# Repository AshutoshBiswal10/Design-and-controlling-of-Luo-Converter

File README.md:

# Comparative Analysis of Control Strategies for Enhancing the Performance of a DC-DC Luo Converter

This repository presents the mathematical modeling, small-signal analysis, controller design, and simulation of a **Positive Output Luo Converter (POLC)** under closed-loop voltage regulation using MATLAB/Simulink.

The project investigates the performance of three different control strategies:

- Proportional-Integral-Derivative (PID)
- Two-Degree-of-Freedom PID (2-DOF PID)
- Three-Degree-of-Freedom PID (3-DOF PID)

The controllers are evaluated based on transient response, overshoot, gain margin, phase margin, and overall voltage regulation performance.

---

## Project Overview

Positive Output Luo Converters (POLCs) are widely employed in renewable energy systems, electric vehicles, and high-gain DC-DC conversion applications due to their high voltage conversion ratio, low output ripple, and positive output polarity.

However, the nonlinear switching dynamics of the converter make accurate voltage regulation challenging under varying input and load conditions.

This project addresses these challenges by:

- Developing a mathematical model of the converter using **state-space averaging**
- Deriving the small-signal control-to-output transfer function
- Designing and comparing PID, 2-DOF PID, and 3-DOF PID controllers
- Evaluating controller performance through time-domain and frequency-domain analyses using MATLAB Sisotool

---

## Methodology

The complete workflow followed in this project is:

1. Develop the Positive Output Luo Converter operating in Continuous Conduction Mode (CCM).
2. Derive the averaged state-space equations.
3. Linearize the nonlinear converter using the state-space averaging technique.
4. Obtain the control-to-output transfer function.
5. Design classical PID, 2-DOF PID, and 3-DOF PID controllers.
6. Tune controller parameters using MATLAB Sisotool.
7. Analyze controller performance using:
   - Step Response
   - Root Locus
   - Bode Plot
8. Compare transient and steady-state characteristics under identical operating conditions.

---

## Technical Specifications

| Parameter | Value |
|-----------|--------|
| Input Voltage | 150 V |
| Output Voltage | 225 V |
| Inductor (L₁, L₂) | 36.04 mH |
| Lift Capacitor (C₁) | 21.40 μF |
| Output Capacitor (C₂) | 30.40 μF |
| Load Resistance | 135.2 Ω |
| Rated Output Power | 440 W |
| Switching Period | 20 μs |

---

## Controllers Implemented

### PID Controller
Conventional feedback controller designed to regulate converter output voltage using proportional, integral, and derivative actions.

### 2-DOF PID Controller
Introduces proportional and derivative set-point weighting to improve reference tracking while reducing overshoot.

### 3-DOF PID Controller
Extends the 2-DOF structure by introducing an additional integral set-point weighting parameter, enabling independent tuning of tracking performance and disturbance rejection.

---

## Performance Comparison

| Controller | Rise Time (s) | Overshoot (%) | Gain Margin (dB) | Phase Margin (°) |
|------------|--------------:|--------------:|-----------------:|-----------------:|
| PID | 0.0186 | 60.2 | 0.0288 | 7.03 |
| 2-DOF PID | 0.0210 | 14.2 | 0.0068 | 70.2 |
| 3-DOF PID | **0.0029** | **30.0** | **0.0231** | **48.9** |

The comparative analysis demonstrates that the **3-DOF PID controller** provides the fastest transient response while maintaining satisfactory stability and improved voltage regulation compared to conventional PID control.

---

## Simulation Results

The repository includes simulation results for:

- Converter output voltage
- Output current
- Input voltage
- Input current
- Inductor current
- Step responses
- Bode plots
- Root locus plots
- Controller performance comparison

---

## Repository Structure

```text
.
├── Hardware/                              # Hardware implementation files and related resources
├── MATLAB Simulation/                     # MATLAB/Simulink models, controller design, and simulations
├── PCB Designing using KiCad/             # PCB schematics and board layout files
├── References/                            # Research papers, datasheets, and supporting literature
├── Results/                               # Simulation plots, controller comparisons, and output waveforms
├── Hardware_Luo_Converter_with_IGBT.slx   # Complete Simulink model of the Luo Converter with closed-loop control
└── README.md
```

### Repository Contents

- **Hardware/** – Hardware implementation resources, component details, and supporting files for the Luo Converter prototype.

- **MATLAB Simulation/** – MATLAB scripts and Simulink models used for small-signal modeling, controller design, transfer function analysis, and simulation.

- **PCB Designing using KiCad/** – KiCad project files including schematic diagrams, PCB layouts, and fabrication-ready design files.

- **References/** – Research papers, datasheets, and reference materials used during the design and analysis of the converter.

- **Results/** – Simulation outputs including step responses, Bode plots, root locus diagrams, output voltage/current waveforms, and controller performance comparisons.

- **Hardware_Luo_Converter_with_IGBT.slx** – Complete MATLAB/Simulink model integrating the Positive Output Luo Converter, IGBT-based switching circuit, and the implemented PID, 2-DOF PID, and 3-DOF PID control strategies.

- **README.md** – Project overview, methodology, simulation details, repository structure, and usage instructions.

---

## Software & Tools

- MATLAB
- Simulink
- MATLAB Sisotool
- Control System Toolbox

---

## Key Features

- State-space averaged modeling of a Positive Output Luo Converter
- Small-signal linearization
- Transfer function derivation
- PID, 2-DOF PID, and 3-DOF PID controller design
- Frequency-domain stability analysis
- Comparative controller evaluation
- MATLAB/Simulink implementation

---

## Future Work

- Fractional-Order PID (FOPID) controller implementation
- Adaptive and intelligent control techniques
- Hardware implementation using DSP or FPGA
- Real-time validation under varying operating conditions
- Efficiency optimization for renewable energy applications

---

## Citation

If you use this work in your research, please cite:

> **Comparative Analysis of Control Strategies for Enhancing the Performance of DC-DC Luo Converters**, IEEE India Council International Subsections Conference (INDISCON), 2025.

---

## Author

**Ashutosh Biswal**

B.Tech, Electrical Engineering

National Institute of Technology Rourkela

MATLAB | Simulink | Control Systems | Power Electronics

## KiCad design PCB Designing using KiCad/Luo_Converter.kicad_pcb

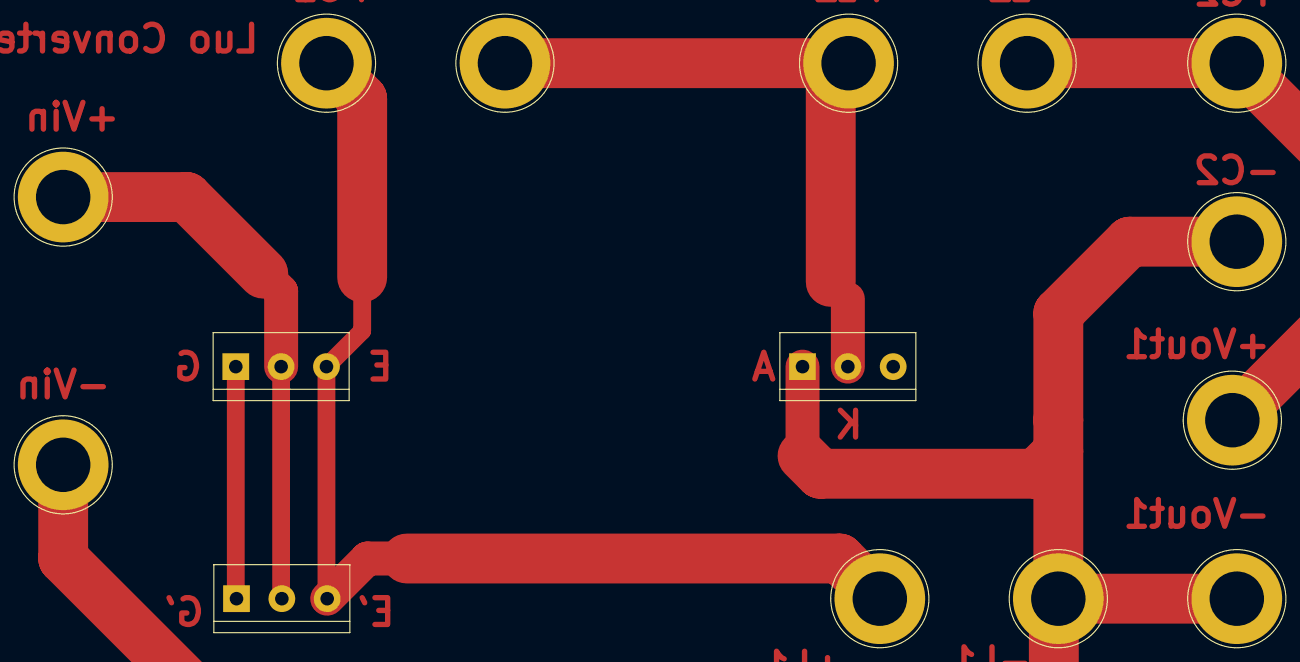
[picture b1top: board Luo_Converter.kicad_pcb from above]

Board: 2 copper layers, 15 parts (0 on the bottom side), 6 nets.

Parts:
+C1, +C2: Screw_Terminal_01x01; Banana_Jack_1Pin
+L1, +L2: Screw_Terminal_01x01; Banana_Jack_1Pin
+Vin: Screw_Terminal_01x01; Banana_Jack_1Pin
+Vout1: Screw_Terminal_01x01; Banana_Jack_1Pin
-C1, -C2: Screw_Terminal_01x01; Banana_Jack_1Pin
-L1, -L2: Screw_Terminal_01x01; Banana_Jack_1Pin
-Vin: Screw_Terminal_01x01; Banana_Jack_1Pin
-Vout1: Screw_Terminal_01x01; Banana_Jack_1Pin
A: Conn_01x03_Pin; TerminalBlock_bornier-3_P5.08mm
E: Conn_01x03_Pin; TerminalBlock_bornier-3_P5.08mm
Sw'1: Conn_01x03_Pin; TerminalBlock_bornier-3_P5.08mm

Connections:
unnamed: +C1.1, +L1.1, E.3, Sw'1.3
unnamed: +C2.1, +Vout1.1, -L2.1
unnamed: +L2.1, -C1.1, A.2
unnamed: +Vin.1, E.2, Sw'1.2
unnamed: -C2.1, -L1.1, -Vin.1, -Vout1.1, A.1
unnamed: E.1, Sw'1.1

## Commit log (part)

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2025-06-30 README.md
2026-03-08 Create tml
